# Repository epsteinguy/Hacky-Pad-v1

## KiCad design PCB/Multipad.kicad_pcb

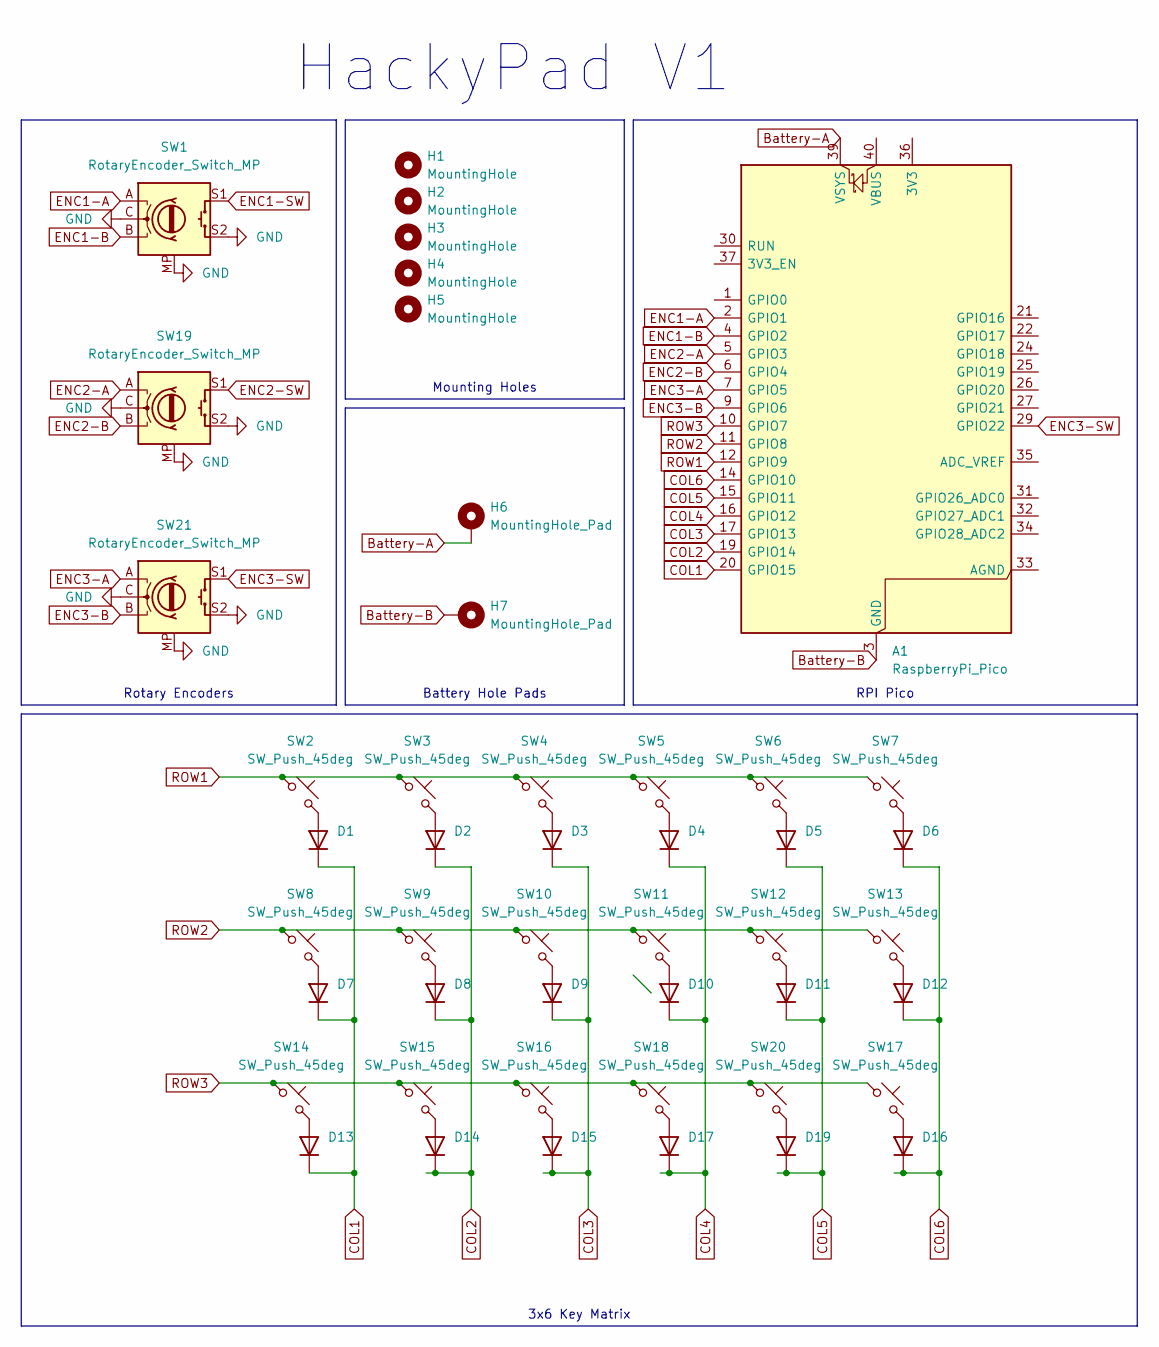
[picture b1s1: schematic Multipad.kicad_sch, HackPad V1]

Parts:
A1: RaspberryPi_Pico; RaspberryPi_Pico_Common_Unspecified
D1, D2, D3, D4, D5, D6, D7, D8, D9, D10, D11, D12, D13, D14, D15, D16, D17, D19: 1N4148; D_DO-35_SOD27_P7.62mm_Horizontal
H1, H2, H3, H4, H5: MountingHole; MountingHole_4mm
H6, H7: MountingHole_Pad; MountingHole_5.5mm_Pad_TopOnly
SW1, SW19, SW21: RotaryEncoder_Switch_MP; RotaryEncoder_Alps_EC11E-Switch_Vertical_H20mm_CircularMoun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
SW2, SW3, SW4, SW5, SW6, SW7, SW8, SW9, SW10, SW11, SW12, SW13, SW14, SW15, SW16, SW17, SW18, SW20: SW_Push_45deg; SW_Cherry_MX_PCB_1.00u

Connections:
Battery-A: A1.39 (VSYS), H6.1
Battery-B: A1.3 (GND), A1.8 (GND), A1.13 (GND), A1.18 (GND), A1.23 (GND), A1.28 (GND), A1.38 (GND), H7.1
COL1: A1.20 (GPIO15), D1.1 (K), D7.1 (K), D13.1 (K)
COL2: A1.19 (GPIO14), D2.1 (K), D8.1 (K), D14.1 (K)
COL3: A1.17 (GPIO13), D3.1 (K), D9.1 (K), D15.1 (K)
COL4: A1.16 (GPIO12), D4.1 (K), D10.1 (K), D17.1 (K)
COL5: A1.15 (GPIO11), D5.1 (K), D11.1 (K), D19.1 (K)
COL6: A1.14 (GPIO10), D6.1 (K), D12.1 (K), D16.1 (K)
ENC1-A: A1.2 (GPIO1), SW1.A
ENC1-B: A1.4 (GPIO2), SW1.B
ENC1-SW: SW1.S1
ENC2-A: A1.5 (GPIO3), SW19.A
ENC2-B: A1.6 (GPIO4), SW19.B
ENC2-SW: SW19.S1
ENC3-A: A1.7 (GPIO5), SW21.A
ENC3-B: A1.9 (GPIO6), SW21.B
ENC3-SW: A1.29 (GPIO22), SW21.S1
GND: SW1.C, SW1.MP, SW1.S2, SW19.C, SW19.MP, SW19.S2, SW21.C, SW21.MP, SW21.S2
unnamed: D1.2 (A), SW2.2
unnamed: D2.2 (A), SW3.2
unnamed: D3.2 (A), SW4.2
unnamed: D4.2 (A), SW5.2
unnamed: D5.2 (A), SW6.2
unnamed: D6.2 (A), SW7.2
unnamed: D7.2 (A), SW8.2
unnamed: D8.2 (A), SW9.2
unnamed: D9.2 (A), SW10.2
unnamed: D10.2 (A), SW11.2
unnamed: D11.2 (A), SW12.2
unnamed: D12.2 (A), SW13.2
unnamed: D13.2 (A), SW14.2
unnamed: D14.2 (A), SW15.2
unnamed: D15.2 (A), SW16.2
unnamed: D16.2 (A), SW17.2
unnamed: D17.2 (A), SW18.2
unnamed: D19.2 (A), SW20.2
ROW1: A1.12 (GPIO9), SW2.1, SW3.1, SW4.1, SW5.1, SW6.1, SW7.1
ROW2: A1.11 (GPIO8), SW8.1, SW9.1, SW10.1, SW11.1, SW12.1, SW13.1
ROW3: A1.10 (GPIO7), SW14.1, SW15.1, SW16.1, SW17.1, SW18.1, SW20.1

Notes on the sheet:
HackyPad V1
Mounting Holes
Battery Hole Pads
Rotary Encoders
3x6 Key Matrix
RPI Pico

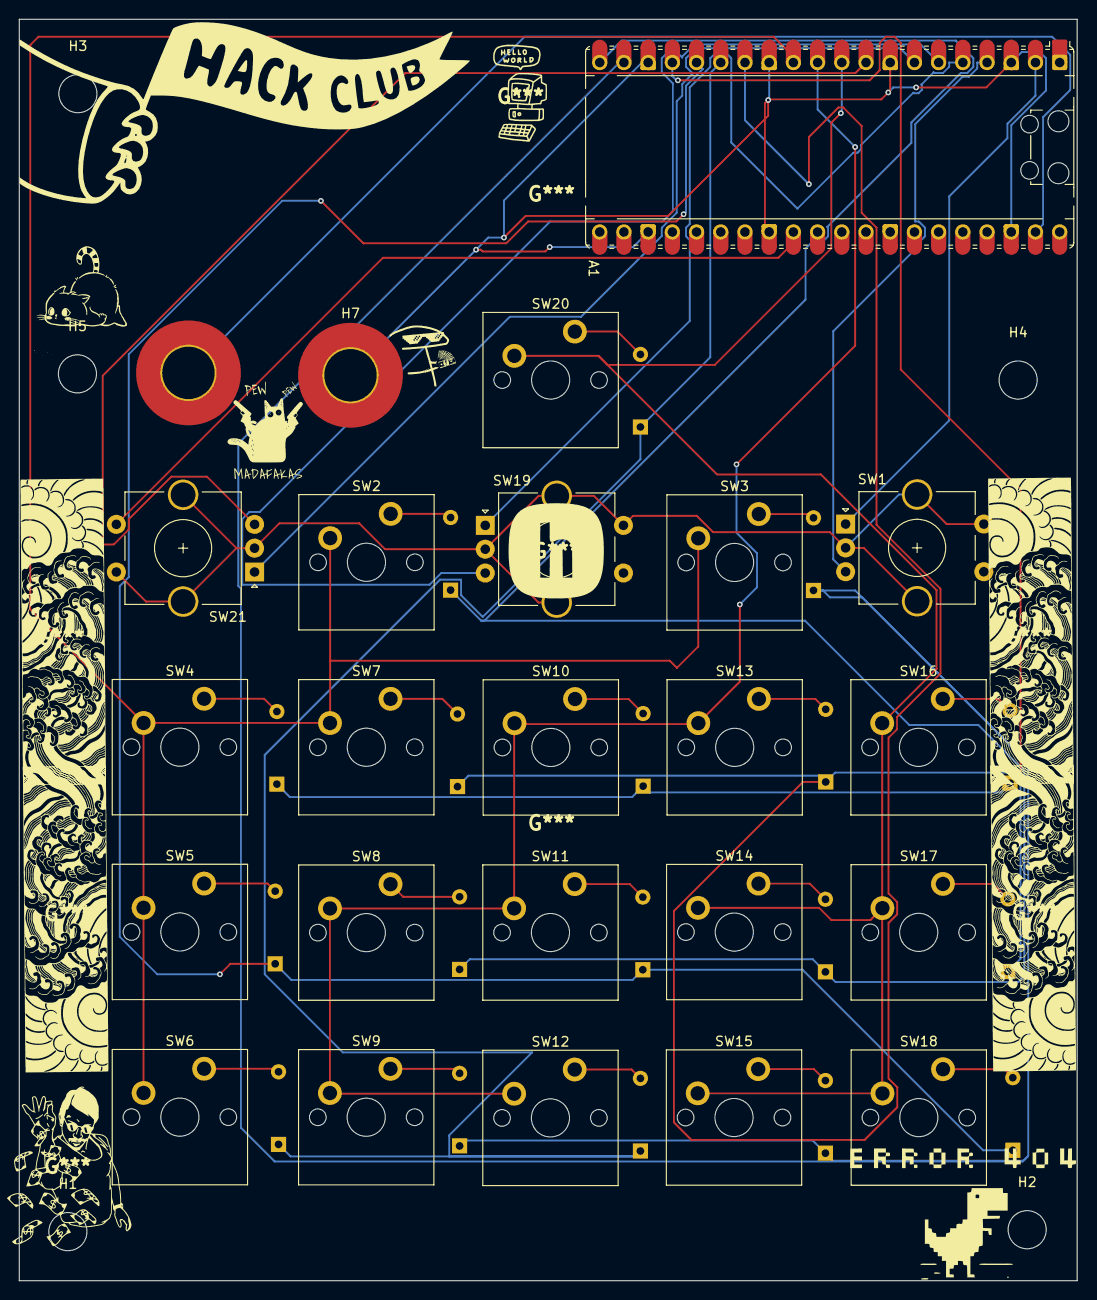
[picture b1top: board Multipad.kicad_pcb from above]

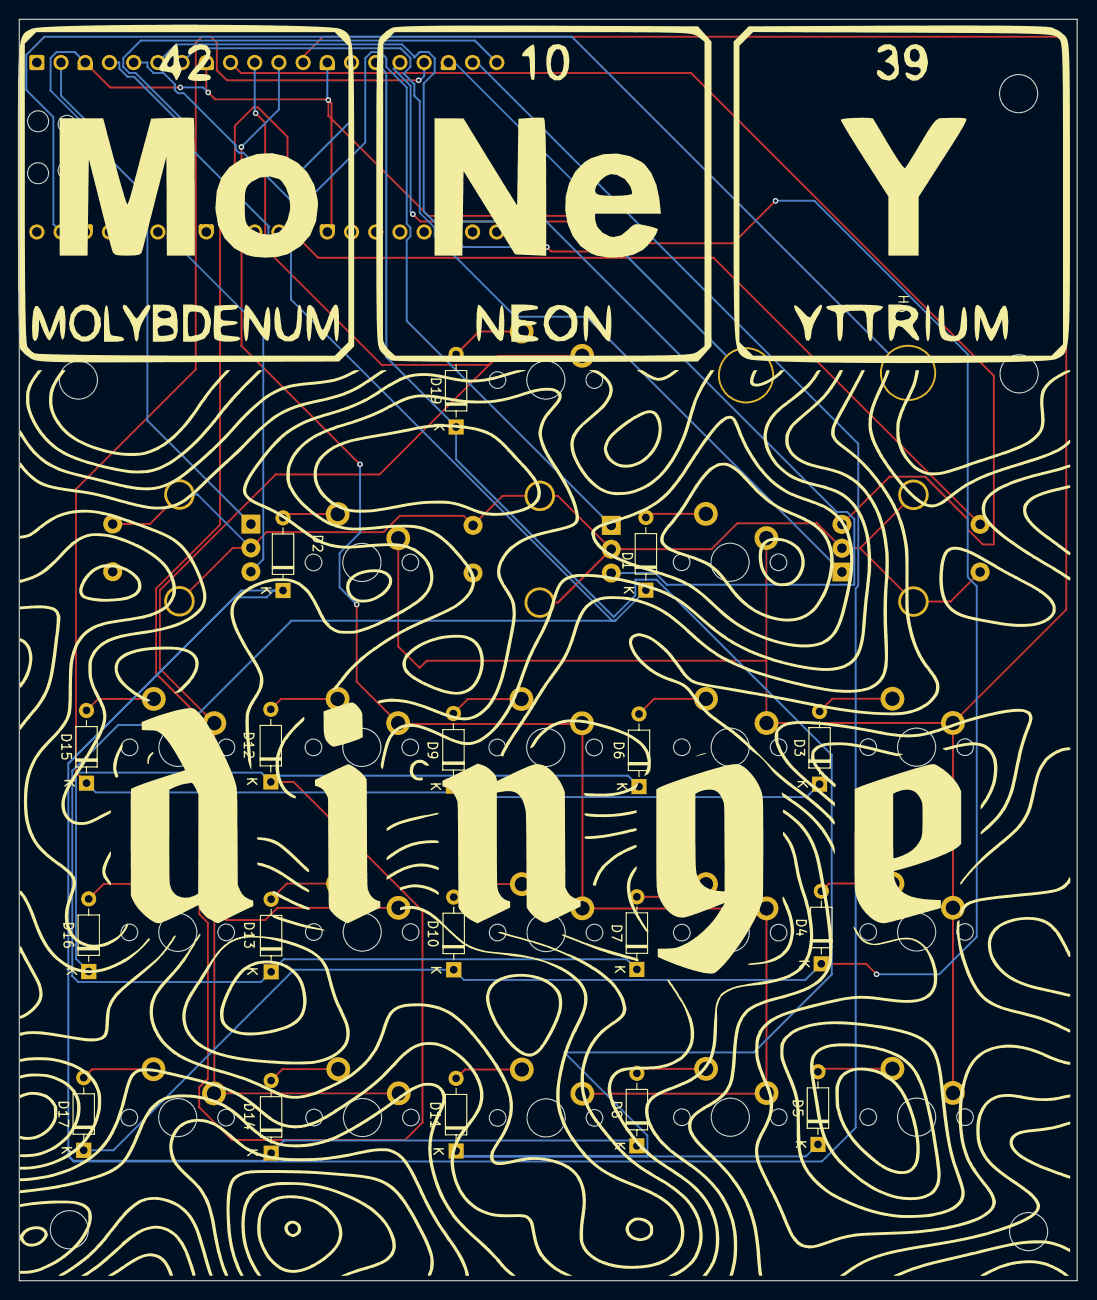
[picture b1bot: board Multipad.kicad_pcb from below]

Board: 2 copper layers, 111.0 x 132.3 mm, 47 parts (18 on the bottom side), 37 nets.

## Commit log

2026-03-03 added images
2026-03-03 Added pcb files
2026-03-03 Added case files
2026-03-05 added cables
2026-03-05 my bad
